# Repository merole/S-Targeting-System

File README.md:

# S-Targeting-System
***Skill Issue***

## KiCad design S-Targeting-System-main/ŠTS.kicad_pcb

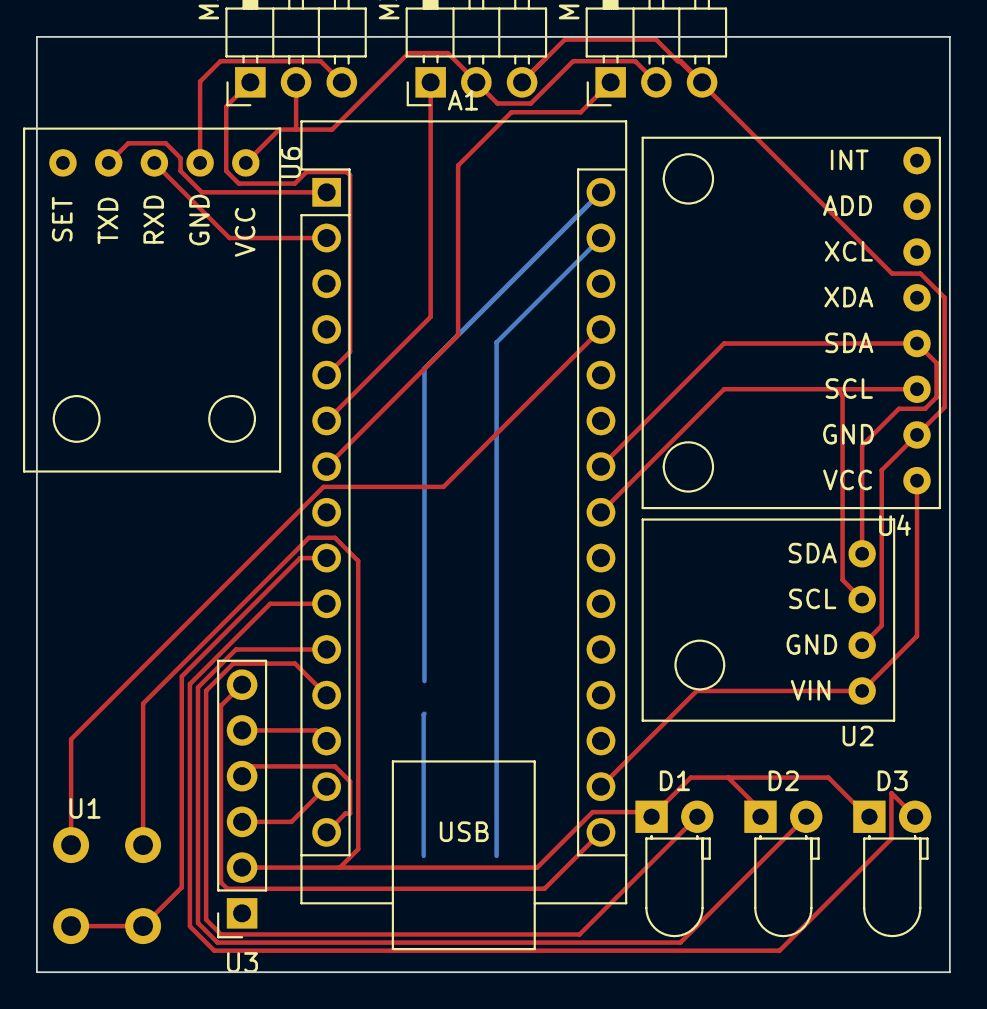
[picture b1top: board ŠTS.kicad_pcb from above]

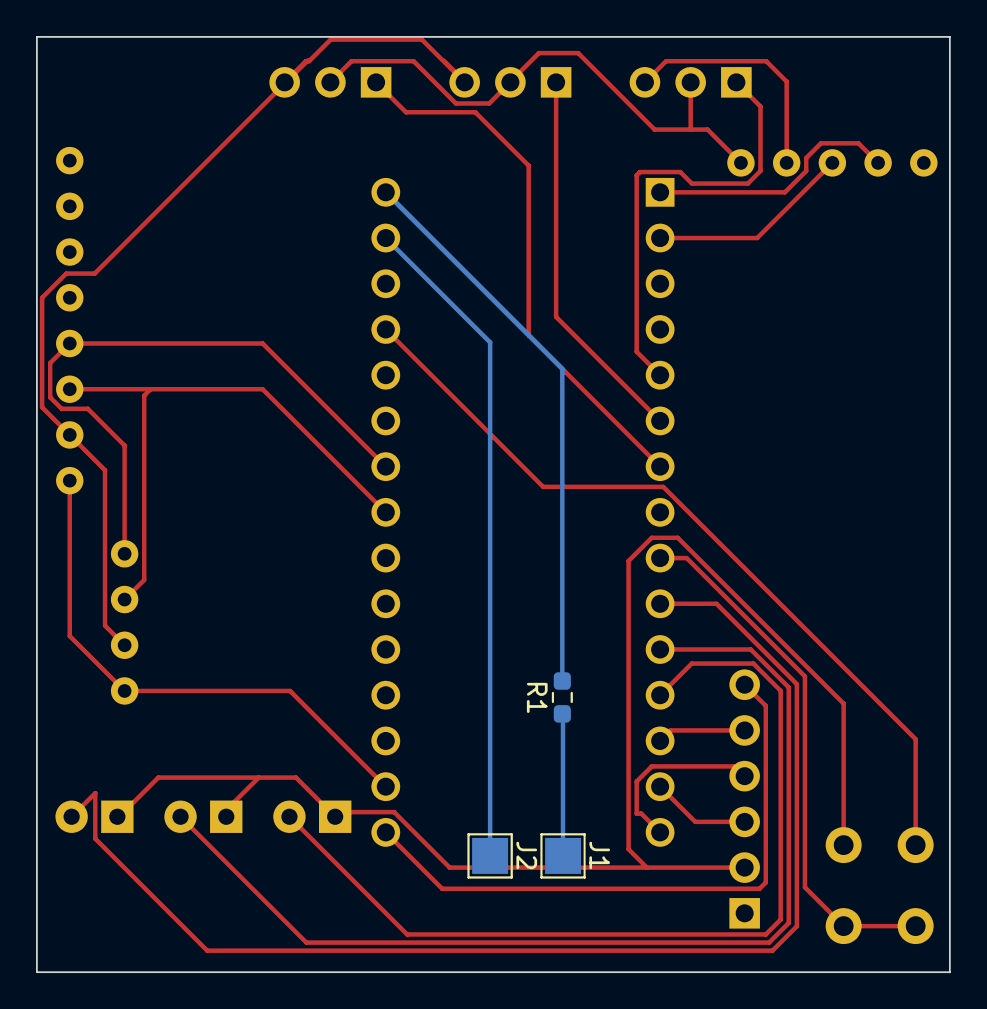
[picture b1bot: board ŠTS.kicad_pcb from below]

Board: 2 copper layers, 50.7 x 52.0 mm, 15 parts (3 on the bottom side), 22 nets.

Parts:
A1: Arduino_Nano_v3.x; Arduino_Nano
D1, D2, D3: LED; LED_D3.0mm_Horizontal_O1.27mm_Z2.0mm
J1, J2: Conn_01x01_Pin; TestPoint_Pad_2.0x2.0mm
M1, M2, M3: Motor_Servo; PinHeader_1x03_P2.54mm_Horizontal
R1: TBD; R_0603_1608Metric_Pad0.98x0.95mm_HandSolder
U1: ADG633YCP; SW_PUSH_6mm_H4.3mm
U2: BMP180; module_bme280_alt
U3: SD_Card_Reader; PinSocket_1x06_P2.54mm_Vertical
U4: module_mpu6050
U6: HC-12; module_bh1750

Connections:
/5V: A1.27 (+5V), M1.2 (+), M2.2 (+), M3.2 (+), U1.1, U3.1 (vcc)
/D2: A1.5 (D2), M2.1 (PWM)
/D3: A1.6 (D3), M3.1 (PWM)
/D4: A1.7 (D4), M1.1 (PWM)
/D6: A1.9 (D6), U1.2
/D7: A1.10 (D7), D3.2 (A)
/D8: A1.11 (D8), D2.2 (A)
/D9: A1.12 (D9), D1.2 (A)
/D10: A1.13 (D10), U3.5 (cs)
/D11: A1.14 (D11), U3.3 (mosi)
/D12: A1.15 (D12), U3.4 (miso)
/D13: A1.16 (D13), U3.6 (sck)
/RX: A1.2 (D0/RX), U6.3 (RXD)
/TX: A1.1 (D1/TX), U6.4 (TXD)
Earth: A1.4 (GND), D1.1 (K), D2.1 (K), D3.1 (K), M1.3 (-), M2.3 (-), M3.3 (-), U3.2 (gnd)
GNDREF: U2.3 (GND), U4.2 (GND), U6.2 (GND)
unnamed: A1.17 (3V3), U2.4 (VIN), U4.1 (VCC), U6.1 (VCC)
unnamed: A1.23 (A4), U2.2 (SCL), U4.3 (SCL)
unnamed: A1.24 (A5), U2.1 (SDA), U4.4 (SDA)
unnamed: A1.30 (VIN), R1.2
unnamed: J1.1, R1.1
unnamed: A1.29 (GND), J2.1

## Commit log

2023-04-04 Edited PCB
2023-04-11 40x60
2023-04-15 switched everyhting for SMT pads
2023-04-24 final
